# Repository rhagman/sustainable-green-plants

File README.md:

The development is currently in alpha, but you can of course try it out.

# Introduction
The goal of this repository is to contain all the information needed to
[get](#how-to-get), [build](#how-to-build) and [run](#how-to-run) an high
pressure aeroponics. The idea is to design a cheap modular system that anyone
can use at home for sustainable food production.

# Small and modular DIY kit
Using a small and modular DIY kit can be very useful for growing herbs or other
small plants you prefer. The parts cost around USD 57 (SEK 500) and to run the
basic kit in the window costs about USD 0.11 (SEK 1) per month. If you, like
me, live in Sweden and need some extra light during winter, you can use LEDs
which can cost you USD 1 (SEK 9) per month - a price example of using LEDs from
IKEA.

## How to get
Go to the [wiki](https://github.com/rhagman/sustainable-green-plants/wiki) and
look under the [small and modular DIY
kit](https://github.com/rhagman/sustainable-green-plants/wiki/Small-and-modular-DIY-kit)
section.

## How to build
Follow the [guide in google photos](https://goo.gl/photos/72PxL2RxAaFRTnkQA).
If you have any questions or need help, you can just comment in the album.

## How to run
In short: mix 10g of
[nutrients](https://github.com/rhagman/sustainable-green-plants/wiki/List-of-materials)
into 4L of water and add it to the vases. Then, you add about 4L of water a
week to the vase and once a month you instead add 4L of the same nutrient mix
as before. [Here](https://goo.gl/photos/Q2npofLhUkbP5R9r5) is an album that I
add pictures to as I'm using it.

# Large and modular DIY kit
Using a large and modular DIY kit can be very useful for growing most plants
that you prefer, this is what you should use for sustainable food production.

## How to get
Go to the [wiki](https://github.com/rhagman/sustainable-green-plants/wiki) and
look under the [large and modular DIY
kit](https://github.com/rhagman/sustainable-green-plants/wiki/Large-and-modular-DIY-kit)
section.

## How to build
Follow the [guide in google photos](https://goo.gl/photos/Ph61oP1ydN2B55Q58).
If you have any questions or need help, you can just comment in the album.

# Software instructions
* arduino_sketch - contains the arduino sketch file which you need to upload to
your arduino uno.

# Get involved
Join our [slack](https://sgplants.slack.com) by sending me a message and I'll
send you an invitation! There have been a lot of different components that have
been tested to make these DIY kits, you can find a [list of
materials](https://github.com/rhagman/sustainable-green-plants/wiki/List-of-materials)
for what has been tested. If you think something should be changed with the
kits, then get in contact with me and we can update the kits!

# License
MIT

# Sustainable Green Plants

[imgur](https://sgplants.imgur.com/) |
[facebook](https://www.facebook.com/sgplants/) |
[twitter](https://twitter.com/sg_plants) |
[blogger](https://sustainablegreenplants.blogspot.se) |
[tumblr](https://sustainablegreenplants.tumblr.com) |
[instagram](https://www.instagram.com/sustainablegreenplants/)

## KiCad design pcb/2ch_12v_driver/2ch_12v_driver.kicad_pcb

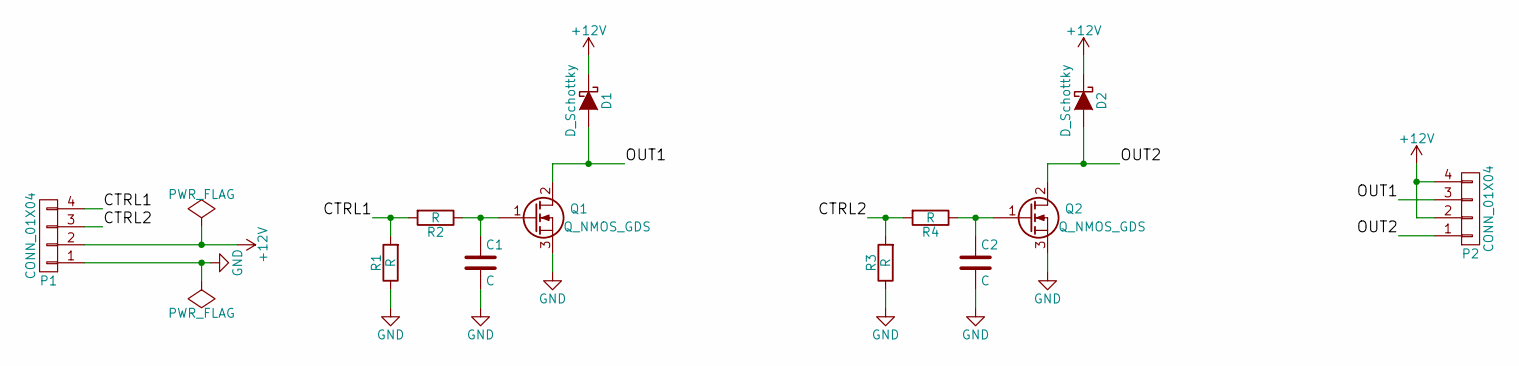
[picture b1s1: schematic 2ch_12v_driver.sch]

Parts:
C1, C2: C; C_Disc_D6_P5
D1, D2: D_Schottky; Diode_DO-41_SOD81_Horizontal_RM10
P1, P2: CONN_01X04; Pin_Header_Straight_1x04
Q1, Q2: Q_NMOS_GDS; TO-220_Neutral123_Vertical
R1, R2, R3, R4: R; Resistor_Horizontal_RM10mm

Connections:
+12V: D1.1 (K), D2.1 (K), P1.2, P2.2, P2.4
/CTRL1: P1.4, R1.2, R2.2
/CTRL2: P1.3, R3.2, R4.2
/OUT1: D1.2 (A), P2.3, Q1.2 (D)
/OUT2: D2.2 (A), P2.1, Q2.2 (D)
GND: C1.2, C2.2, P1.1, Q1.3 (S), Q2.3 (S), R1.1, R3.1
unnamed: C1.1, Q1.1 (G), R2.1
unnamed: C2.1, Q2.1 (G), R4.1

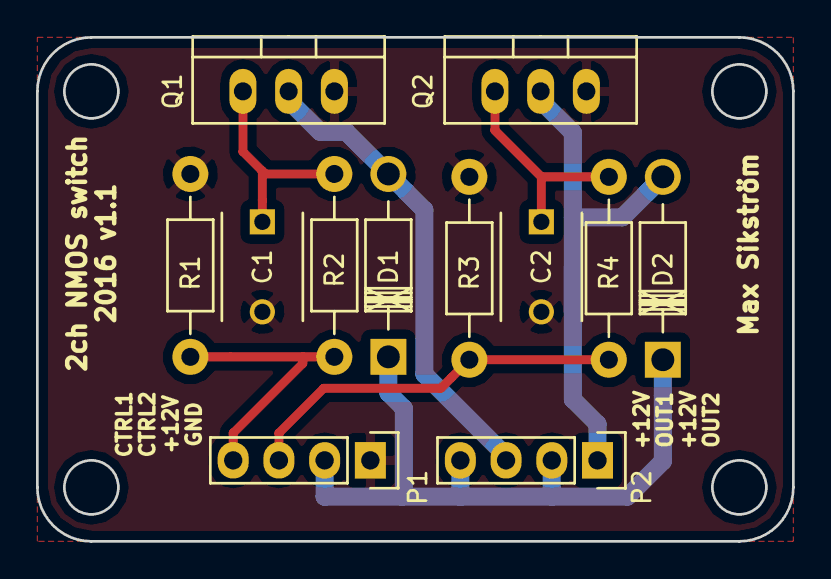
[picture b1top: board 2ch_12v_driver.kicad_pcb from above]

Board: 2 copper layers, 42.0 x 28.0 mm, 12 parts (0 on the bottom side), 8 nets.

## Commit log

2015-08-16 Initial commit with contributors
2015-08-16 Added the arduino file to the project
2015-08-16 Added the processing file to the project
2015-08-16 Added the gnuplot file to the projekt
2015-12-29 Add README and gitignore file
2016-01-01 Add MIT license file and update README
2016-01-10 Add working with now section
    Thought it would be nice to have a section where I'll add information of what I'm working with now and what will be next.
2016-01-17 Add 3d-printing folder, stl file and update README
    The folder will hold all 3d-printed related stuff. I would like to be able to
    build the systemes with or without a 3d-printer. Upload the stl-file for the
    pet-connector.
2016-01-17 Update README
    Make "Software instructions" into a list.
2016-09-04 Move arduino dir
    The name of the directory and sketch file needs to be the same.
    Otherwise the arduino IDE will complain.
2016-10-22 Move arduino file and update measure interval
    The arduino file should be within a directory with the same name as the .ino file. Right now I do not care about the measure interval so set it to one hour.
2016-10-22 Clean up things no longer needed
    I've decided to clean up some unused things since my main focus now is to
    get a useful prototype up and running.
2016-10-23 Implement good default behavior
    After uploading the sketch to the Arduino you should be able to just plug
    everything in and it should work well for a simple system.
    Assume that the time is 10:00 and run the pump every day at 10:00 and
    20:00 for at most one minute. Spray every 10 min for 2 sec each.
    Refactor some of the horrible code. Next step will probably be to add unit
    and integration tests.
2016-10-24 PCB: Add 2ch 12V driver, to power pump from mcu
    To be able to drive a 12V inductive load from a microcontroller like
    Arduino, a driver circuit is needed.
    This adds a two channel with about 5V input (can be anything from NMOS V_th
    voltage to V_gs maximum voltage), to power the output load.
2016-10-24 Add a testing framework and build for atom
    I came a cross a nice package for atom that seems to do everything I would
    like to do with the old arduino IDE. Installed "platformio-ide" for atom
    and changed the code to fit into how they whant it.
2016-11-06 Typo
2017-01-02 Set theme jekyll-theme-cayman
2017-01-12 Update the file for travis
2017-01-12 initial autotools setup
2017-01-19 use foreign to not require GNU specific files
2017-01-19 autoreconf before Travis' standard building process
2017-01-21 Update README.md
    Remove dashes from the first header since it looks nicer on the github pages.
    Add an image of the basic kit version in the window, the image is hosted on Dropbox. Better than nothing.
    Add link to the shared Dropbox folder with a lot if different images of the project.
2017-01-22 Create CNAME
2017-01-22 Image of the basic kit
    Would be nice to have a picture of the build so add one in the img folder
    in doc. The doc dir will later be used to store the github pages for this
    project.
2017-01-22 Update README.md
    Add a working image to the readme, might be a bit big...
2017-02-06 Move doc to docs
    GitHub can can point to docs for github pages. Move the doc folder so that
    we follow that standard that GitHub follows.
2017-02-06 Remove pH measurement functionality
    The focus is not to have a lot of sensors at the moment. Building for
    d1_mini got errors for eeprom so this is the perfect time to remove some
    unused code. Later in the project I will re-add the functionality.
2017-02-06 Use PlatformIO and Travis
    PlatformIO seems like a good tool to use since I easily can build for
    Arduino UNO and D1 mini. As well as other platforms in the future. Nice
    support for it in the Atom IDE that I have started to like more and more.
    Also, implement the use of Travis.
2017-02-06 Add status image for Travis to the README
2017-02-23 Update the title of gh-pages
2017-03-04 Add flair and social media links
2017-03-04 Update default settings
    We now run the system with the same schedule and settings all the time.
    When the microcontroller starts it assumes that the time is 20:00 and it
    runs the pump. Then every 20min it sprays the roots for 2s.
    Also make some style changes to the code and clean up a k = k++ wtf...
2017-03-05 Update defaults
2017-04-24 Add feature testing
    A lot of user like it when "It just works".
    Provide good default settings for the users that just uploads the software to
    the micro controller and plugs it in to a power supply. The settings are
    optimized for robustnes and ease of use.
2017-08-06 Update the image for the small and modular diy kit
2017-08-06 General update of the README
    Change all links to google photo instead of dropbox. Add information about
    the Large and modular diy kit. I think we need to find a better name for
    these things soon...
2018-01-31 Breaking change: change pin output
    So that it works nicely with arduino uno and wemos. Also, remove legacy
    code that is no longer needed.
2019-03-08 Default values for nozzles and pump duration
2019-08-12 First stab at validating wiki
2019-08-13 More thorough link checking
2019-08-13 markdown extractor had trouble with python2
2019-08-13 Skip amazon links
2019-08-13 remove accidental jobs
